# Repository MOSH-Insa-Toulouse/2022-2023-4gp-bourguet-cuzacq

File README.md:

# Projet Capteur de Solène Bourguet et Victor Cuzacq
_Ce projet s’inscrit dans le contexte de l’UF « Du capteur au band de test en open source hardware » du département de Génie Physique de l’INSA Toulouse._  

## Objectif :  
Ce projet se base sur les travaux des chercheurs : Cheng-Wen Lin, Zhibo Zhao, Jaemyung Kim et Jiaxing Huang, afin d’évaluer les potentialités de leur technologie low-tech, le « Pencil Draw Strain Gauges ». L’objectif de ce projet est de réaliser un capteur low-tech à base de graphite et d’en faire une analyse critique argumentée pour en cerner les potentialités et le cas échéant proposer des solutions d’amélioration.  

Pour ce capteur nous utilisons une feuille sur laquelle nous avons dessiner au crayon de papier. La contrainte mécanique appliquée sur la feuille va ainsi modifier la distance entre les particules de graphique et par conséquent la résistance au passage du courant.  

Les étapes et le matériel nécessaire à ce projet sont détaillés ci-dessous.  

## Sommaire  
1. [Livrables](https://github.com/MOSH-Insa-Toulouse/2022-2023-4gp-bourguet-cuzacq#1-livrables)    
2. [Matériel requis](https://github.com/MOSH-Insa-Toulouse/2022-2023-4gp-bourguet-cuzacq#2-mat%C3%A9riel-requis)  
3. [Simulation sur LTSpice](https://github.com/MOSH-Insa-Toulouse/2022-2023-4gp-bourguet-cuzacq#3-simulation-sur-ltspice)  
4. [Kicad](https://github.com/MOSH-Insa-Toulouse/2022-2023-4gp-bourguet-cuzacq#4-kicad)    
  1 [Symboles et empreintes de composants](https://github.com/MOSH-Insa-Toulouse/2022-2023-4gp-bourguet-cuzacq#41-symboles-et-empreintes-de-composants)  
  2 [Schématique](https://github.com/MOSH-Insa-Toulouse/2022-2023-4gp-bourguet-cuzacq#42-sch%C3%A9matique)  
  3 [Placement des composants](https://github.com/MOSH-Insa-Toulouse/2022-2023-4gp-bourguet-cuzacq#43-placement-des-composants)    
  4 [Visualisation 3D](https://github.com/MOSH-Insa-Toulouse/2022-2023-4gp-bourguet-cuzacq#44-visualisation-3d)  
5. [Fabrication du shield](https://github.com/MOSH-Insa-Toulouse/2022-2023-4gp-bourguet-cuzacq#5-fabrication-du-shield)    
  1 [Réalisation du PCB](https://github.com/MOSH-Insa-Toulouse/2022-2023-4gp-bourguet-cuzacq#51-r%C3%A9alisation-du-pcb)    
  2 [Perçage et soudure de nos composants](https://github.com/MOSH-Insa-Toulouse/2022-2023-4gp-bourguet-cuzacq#52-per%C3%A7age-et-soudure-de-nos-composants)    
6. [Arduino](https://github.com/MOSH-Insa-Toulouse/2022-2023-4gp-bourguet-cuzacq#6-arduino)    
  1 [Bibliothèques utilisées](https://github.com/MOSH-Insa-Toulouse/2022-2023-4gp-bourguet-cuzacq#61-biblioth%C3%A8ques-utilis%C3%A9es)    
  2 [Code Arduino](https://github.com/MOSH-Insa-Toulouse/2022-2023-4gp-bourguet-cuzacq#62-code-arduino)    
7. [Application Android](https://github.com/MOSH-Insa-Toulouse/2022-2023-4gp-bourguet-cuzacq#7-application-android)  
8. [Banc de test](https://github.com/MOSH-Insa-Toulouse/2022-2023-4gp-bourguet-cuzacq#8-banc-de-test)    
  1 [Banc de test](https://github.com/MOSH-Insa-Toulouse/2022-2023-4gp-bourguet-cuzacq#81-banc-de-test-1)    
  2 [Résultats obtenus](https://github.com/MOSH-Insa-Toulouse/2022-2023-4gp-bourguet-cuzacq#82-r%C3%A9sultats-obtenus)    
  3 [Analyse des résultats](https://github.com/MOSH-Insa-Toulouse/2022-2023-4gp-bourguet-cuzacq#83-analyse-des-r%C3%A9sultats)    
9. [Pistes d’améliorations](https://github.com/MOSH-Insa-Toulouse/2022-2023-4gp-bourguet-cuzacq#9-pistes-dam%C3%A9liorations)     
10. [Datasheet](https://github.com/MOSH-Insa-Toulouse/2022-2023-4gp-bourguet-cuzacq#10-datasheet)   

## 1. Livrables  
Voici l’ensemble des livrables du projet :  
- Une carte PCB se connectant à un module Arduino UNO contenant un amplification transimpédance, un module Bluetooth, un écran OLED et un Flex sensor  
-	Un code Arduino permettant de mesurer la déformation du capteur et de piloter un module Bluetooth, un écran OLED et un Flex sensor  
-	Une application Android APK  
-	Un protocole de test (simulation sous LTspice + banc de test ?)  
-	La datasheet du capteur de déformation  

Nous avons commencé par réaliser la modélisation de notre shield sur le logiciel Kicad. Il contient ainsi un amplificateur transimpédance, un écran OLED, un module Bluetooth et un Flex sensor. Nous avons ensuite fabriqué par lithographie notre carte PCB et ajouté les composants par soudage sur la carte après l’avoir percée au préalable. 
Nous avons réalisé un code Arduino permettant de mesurer la variation de résistance du capteur et de piloter un module Bluetooth, un écran OLED et un Flex sensor.  

En parallèle de cela, nous avons créé une application Android grâce au logiciel MIT App Inventor, capable de communiquer avec le module Bluetooth et recevoir la valeur de la tension de sortie et de calculer les valeurs de résistances de notre capteur.  

Par la suite nous avons mis en place un banc de test pour caractériser notre capteur en fonction de sa déformation et de la mine de crayon utilisée (HB, B).   

Pour finir nous avons réalisé une datasheet à l’aide des résultats obtenus par le banc de test.   

## 2. Matériel requis

Voici la liste des composants nécessaires à l’élaboration de notre capteur   

-	2 résistances 100kΩ (R1 et R3)    
-	1 résistance 10kΩ (R5) (R4 sur notre Kicad)  
-	2 résistances 1kΩ (R2 et R6) (R2 et R5 sur notre Kicad)  
-	1 résistance de 33kΩ (Rflex)  
-	1 capacité 1µF (C4)  
-	2 capacités 100nF (C1 et C2)   
-	1 amplificateur opérationnel LTC1050  
-	1 module Bluetooth HC05   
-	1 écran OLE I2C 0.91  
-	1 Flex sensor   
-	1 feuille de papier  
-	3 crayon de papier : HB, B  

## 3. Simulation sur LTspice 

Le capteur graphique que nous souhaitons réalisé est alimenté en 5V et sa résistance fluctue entre 20 et 100MΩ, ainsi le courant en sortie sera de l’ordre de 100nA (I =U/R). Ce courant de sortie sera trop faible pour être capté par la carte Arduino UNO, c’est pourquoi nous devons utiliser un amplificateur transimpédance, pour amplifier le signal de sortie de notre capteur. 

Ce montage gère à la fois l’amplification et le filtrage du signal pour limiter l’amplification du bruit.

Voici la fonction des différents composants :
  - R5 en entrée protège l'ampli opérationnel contre les décharges électrostatiques, en forme avec C1 un filtre pour les bruits en tension  
  - C1 avec R1 forme un filtre pour le bruit en courant  
  - R2 sera interchangeable, pour permettre une adaptation du calibre  
  - C4 avec R3 forme un filtre actif  
  - C2 avec R6 forme le filtre de sortie 
  
On peut calculer la résistance du capteur grâce à la formule :

$R_{Capteur} = (1 + \dfrac{R3}{R2}) \times R1 \times (\dfrac{VCC}{VADC}) - R1 - R5$  

Dans notre code Arduino ainsi que dans notre Kicad, notre R4 est égale au R5 du schéma ci-contre et R5 vaut R6 du schéma.   

## 4. Kicad

Nous avons modélisé notre shield PCB sur le logiciel KICAD. Nous avons commencé par dessiner tous les composants puis nous avons créé leur empreinte.  

### 4.1 Symboles et empreintes de composants   

- Amplificateur LTC1050  

- Ecran OLED  

- Flex sensor  

- Module Bluetooth HC05  

### 4.2 Schématique  

Une fois les empreintes créées, nous avons réalisé le schéma de notre shield.  

### 4.3 Placement des composants  

### 4.4 Visualisation 3D  

Nous avons téléchargé les modèles 3D de nos composants afin de visualiser notre PCB en 3D et de vérifier que les composants de la carte ne se chevauchent pas.   

## 5. Fabrication du shield  

### 5.1 Réalisation du PCB  

Nous avons réalisé notre PCB avec l’aide de Catherine Crouzet au sein du département du Génie Physique et du Génie Electrique et Informatique de l’INSA Toulouse. Pour fabriquer notre PCB nous avons utilisé une plaquette d’époxy recouverte d’une fine couche de cuivre. Nous avons d’abord imprimé notre modélisation du PCB réalisé sur Kicad. Nous avons ensuite plongé notre plaquette avec notre modélisation imprimée dans une machine insolant des UVs.  
Notre modélisation imprimée va servir de masque lors de cette insolation sous UVs. A l’aide d’un révélateur, nous avons retiré la partie de la résine non insolée. Nous plongeons ensuite la plaquette dans un bain de perchlorure de fer pour la gravure. Le cuivre non protégé par la résine est éliminé. Pour finir, nous lavons notre plaquette à l’acétone pour éliminer les dernières traces de résine.   

### 5.2 Perçage et soudure de nos composants   

Nous perçons ensuite notre PCB à l’aide d’une perceuse électrique pour insérer nos composants. Le diamètre de nos percage varie selon le type de composant :   
-	0,8 mm : pour l’AOP LTC1050, le module OLED, Bluetooth, le Flex sensor, les résistances et les capacités
-	1,0 mm : pour les broches de connexion de la carte Arduino UNO.  
Nous avons soudé nos composants sur la face arrière du PCB. Nous avons cependant constaté des courts-circuits sur la carte PCB qui nous ont obligé à souder des fils reliés à la masse sur la face avant de notre PCB.  

## 6. Arduino  

### 6.1 Bibliothèques utilisées    

Nous avons utilisé 3 bibliothèques dans notre code Arduino :  
-	Wire.h : qui s’occupe de la communication avec l’écran OLED ;  
-	SoftwareSerial.h : pour définir les ports utilisés par le module Bluetooth ;  
-	Adafruit_SSD1306.h : afin de contrôler notre écran OLED.   

### 6.2 Code Arduino   

Notre code permet de récupérer la tension à la sortie du capteur et de calculer la valeur de sa résistance. Nous avons rajouté des éléments sur le shield pour faciliter la communication de l’information :    
-	Un écran OLED : l’écran reçoit la valeur de la résistance (en MΩ) du capteur en continu 
-	Un module Bluetooth : qui envoie les données à l’application  
-	Un Flex sensor : dont la valeur de la résistance et la valeur de son angle sont affichés dans le Serial Monitor. Sa présence nous permet de vérifier les démarches réalisées sur le capteur.  

## 7. Application Android   

Nous avons créé une application android sur Mit App Inventor que nous avons pu télécharger via le .apk du dossier. 
Le but de notre application est d’afficher la valeur de la tension de sortie du capteur en continu sur un téléphone Android et de tracer un graphique de la valeur de sa résistance en fonction du temps. C’est l’application qui va calculer la valeur de la résistance du capteur. 
Notre interface comprend :  
-	Un bouton connexion au Bluetooth de notre shield. Il devient vert quand la connexion est établie et grise quand elle ne l’est pas.   
-	Un bouton déconnexion au Bluetooth. Il devient rouge quand on appuie dessus.  
-	La valeur de la tension de sortie du capteur en continu.   
-	Un graphique affichant la valeur de la résistance de notre capteur en fonction du temps.   

## 8. Banc de test   

### 8.1 Banc de test   

Nous avons testé notre capteur sur un banc de test disponible au Génie Physique de l’INSA Toulouse. Notre banc de test composé de 7 demi cylindres de rayon allant de 2,5cm à 1cm par pas de 0,5cm.   

En enrobant les cylindres avec notre capteur, nous créons une déformation que nous pouvons calculer avec la formule :   

$\epsilon = \dfrac{e}{2 \times R_{Capteur}}$   

avec l’épaisseur du papier : e = 0,3 mm et l’angle de la deformation : θ  

et $R_{Capteur} = \dfrac{d}{2 \times θ}$  

La contrainte mécanique (compression ou expansion) appliquée au papier va modifier la distance entre les particules de graphite et donc la résistance au passage du courant :  
-	Lorsque l’on enrobe le cylindre avec la face recouverte de graphite vers le haut, nous appliquons une tension ou expansion à notre papier, ainsi les particules de graphite se retrouve plus éloignées. Par conséquent le courant circule moins facilement et la valeur de la résistance augmente.   
-	A l’inverse, lorsque l’on enrobe le cylindre avec la face recouverte de graphite contre le cylindre, nous appliquons une compression à notre papier, ainsi les particules de graphite se rapprochent. Par conséquent le courant circule plus facilement et la valeur de la résistance diminue.   

_Attention : Plus nous utilisons la jauge de contrainte, plus nous l’abîmons. En effet, la quantité de graphite diminue avec le temps à cause du frottement des pinces en métal ou des doigts avec le papier._   

### 8.2 Résultats obtenus  

La caractérisation de notre capteur est basé sur la mesure des variations de la résistance dû à la déformation.  

### 8.3 Analyse des résultats   

Les résultats obtenus semblent cohérents. En effet, on observe bien une résistance qui diminue lorsqu’on applique une compression au capteur. Par conséquent ΔR (=R-R0) diminue plus la déformation est grande. Et à l’inverse on observe une résistance grandissante lorsqu’on applique une expansion à notre capteur. Par conséquent ΔR (=R-R0) augmente plus la déformation est importante.  

De plus, en fonction du type de crayon utilisé, les variations de résistances changent. En effet, si un crayon est considéré comme gras c’est qu’il dépose plus de graphite sur le papier. Par conséquent le courant aura plus de facilité à passer et donc la résistance sera plus faible. Ainsi nous pouvons constater que les crayons de type B sont plus gras que les crayons de type HB.   

### 8.4 Comparaison avec le flex sensor  

Nous avons analysé la variation de la résistance du flex sensor pour le comparer avec notre capteur. Nous pouvons constater que le flex sensor possède une valeur de résistance plus importante que notre capteur de graphite.   

## 9. Pistes d'améliorations 

Certains points de notre banc de test peuvent être remis en question :  
-	Le dépôts de graphite est difficile à maîtriser. Par conséquent il est impossible de créer plusieurs jauge de contraintes identiques. De plus, la quantité de graphite diminue avec le temps à cause du frottement des pinces en métal ou des doigts avec le papier.  
-	Nous aurions pu rajouter sur notre shield un potentiomètre digital qui nous aurait permis de pouvoir analyser une gamme de résistance plus grande.   

## 10. Datasheet  

La datasheet de notre capteur est disponible [ICI](https://github.com/MOSH-Insa-Toulouse/2022-2023-4gp-bourguet-cuzacq/blob/main/Datasheet/Datasheet_low_tech_graphitr_based_on_strain_sensor.pdf).  

### Remerciement et contact 

Nous souhaiterions remercier Catherine Crouzet qui nous a beaucoup aidé à comprendre et à solutionner nos problèmes tout au long du projet.  

Pour toutes questions ou informations supplémentaires, vous pouvez nous contacter par mail :  
-	Solène BOURGUET : bourguet@insa-toulouse.fr   
-	Victor CUZACQ : cuzacq@insa-toulouse.fr

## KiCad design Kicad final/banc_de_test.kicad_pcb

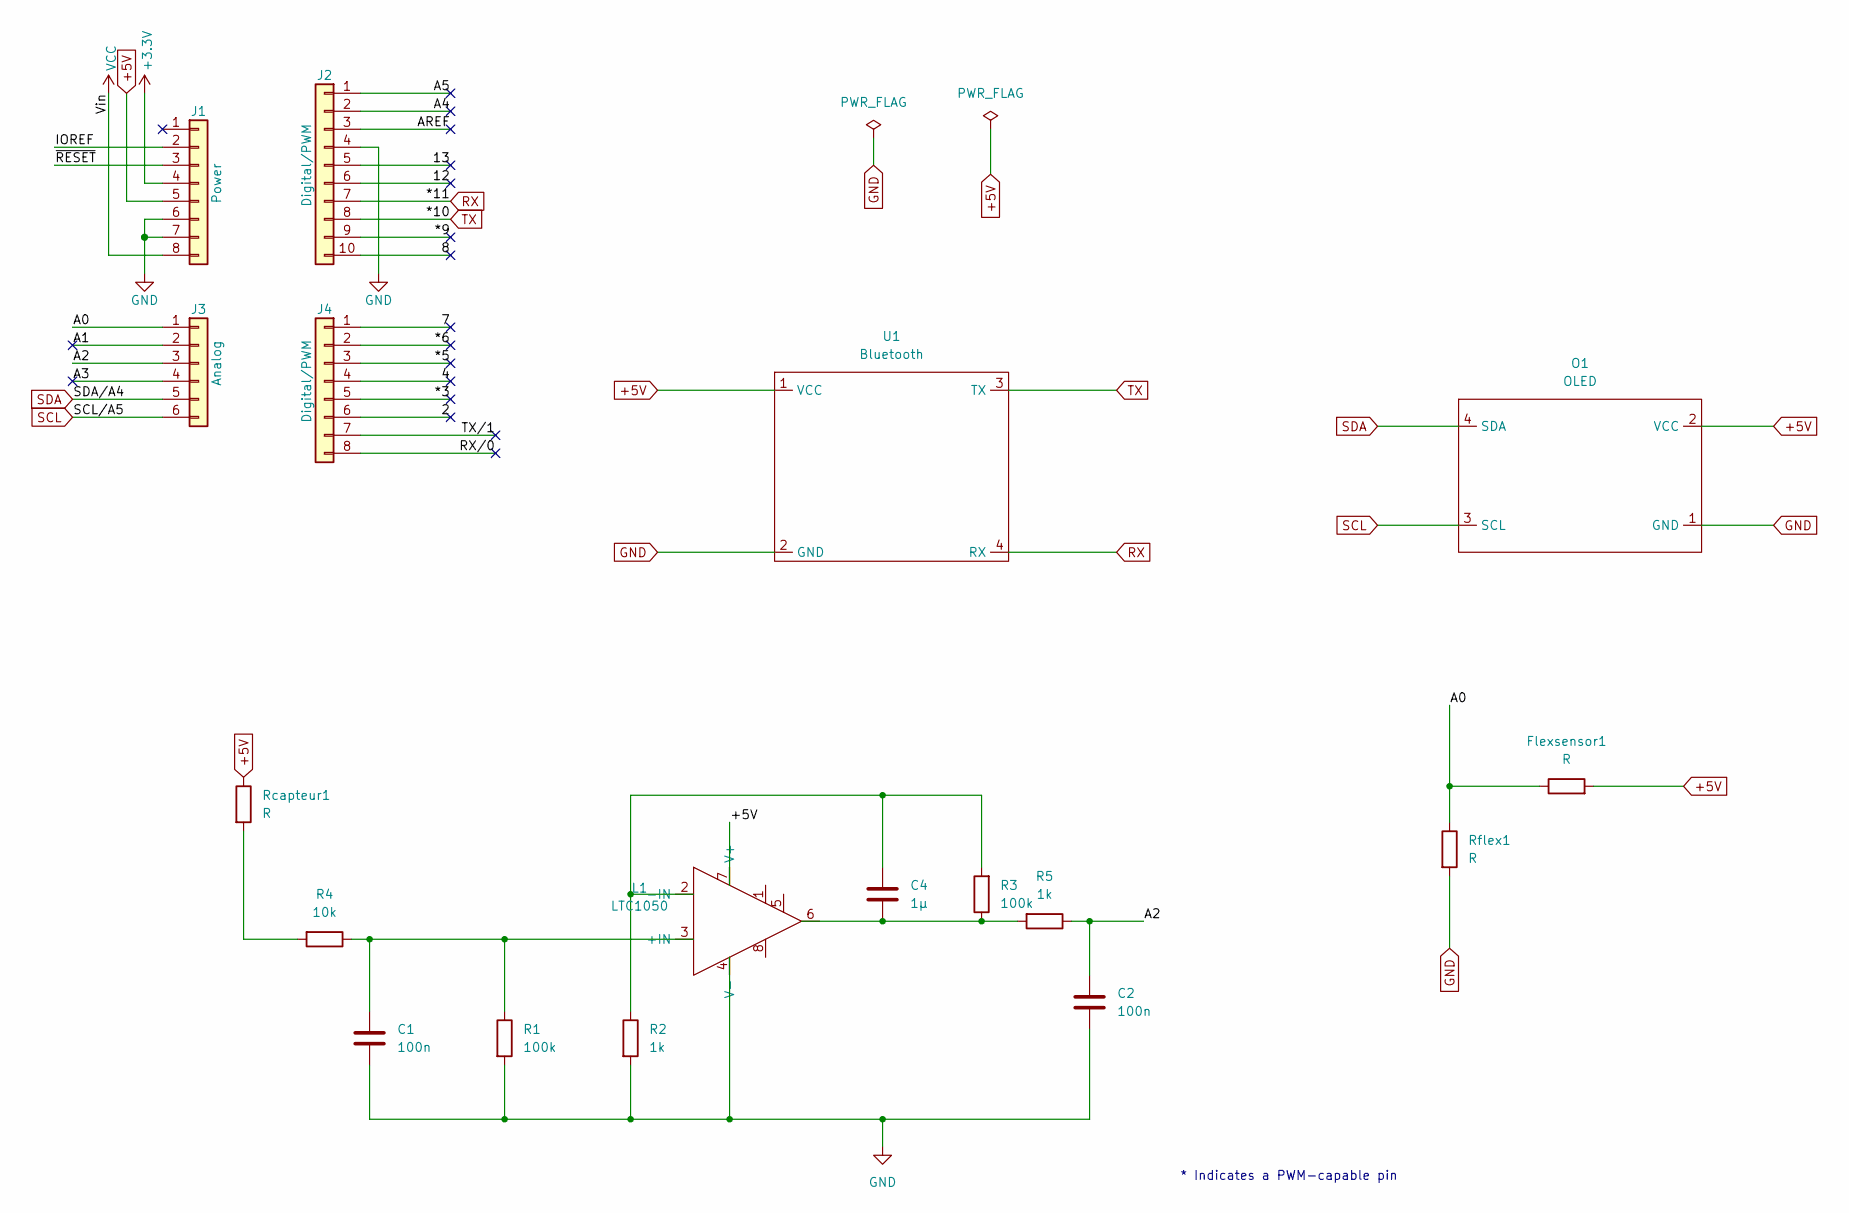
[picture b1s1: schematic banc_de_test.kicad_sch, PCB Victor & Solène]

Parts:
C1, C2: 100n; C_Disc_D3.0mm_W1.6mm_P2.50mm
C4: 1µ; C_Rect_L7.0mm_W4.5mm_P5.00mm
Flexsensor1: R; R_Axial_DIN0204_L3.6mm_D1.6mm_P2.54mm_Vertical
J1: Power; PinSocket_1x08_P2.54mm_Vertical
J2: Digital/PWM; PinSocket_1x10_P2.54mm_Vertical
J3: Analog; PinSocket_1x06_P2.54mm_Vertical
J4: Digital/PWM; PinSocket_1x08_P2.54mm_Vertical
L1: LTC1050
O1: OLED
R1, R3: 100k; R_Axial_DIN0204_L3.6mm_D1.6mm_P2.54mm_Vertical
R2, R5: 1k; R_Axial_DIN0204_L3.6mm_D1.6mm_P2.54mm_Vertical
R4: 10k; R_Axial_DIN0204_L3.6mm_D1.6mm_P2.54mm_Vertical
Rcapteur1: R; R_Axial_DIN0204_L3.6mm_D1.6mm_P2.54mm_Vertical
Rflex1: R; R_Axial_DIN0204_L3.6mm_D1.6mm_P2.54mm_Vertical
U1: Bluetooth

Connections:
+3V3: J1.4
+5V: Flexsensor1.2, J1.5, L1.7 (V+), O1.2 (VCC), Rcapteur1.1, U1.1 (VCC)
/2: J4.6
/4: J4.4
/7: J4.1
/8: J2.10
/12: J2.6
/13: J2.5
/*3: J4.5
/*5: J4.3
/*6: J4.2
/*9: J2.9
/A0: Flexsensor1.1, J3.1, Rflex1.1
/A1: J3.2
/A2: C2.1, J3.3, R5.1
/A3: J3.4
/A4: J2.2
/A5: J2.1
/AREF: J2.3
/IOREF: J1.2
/RX/0: J4.8
/TX/1: J4.7
/~RESET: J1.3
GND: C1.2, C2.2, J1.6, J1.7, J2.4, L1.4 (V-), O1.1 (GND), R1.2, R2.2, Rflex1.2, U1.2 (GND)
unnamed: C1.1, L1.3 (+IN), R1.1, R4.1
unnamed: C4.1, L1.2 (-IN), R2.1, R3.2
unnamed: C4.2, L1.6, R3.1, R5.2
unnamed: R4.2, Rcapteur1.2
RX: J2.7, U1.4 (RX)
SCL: J3.6, O1.3 (SCL)
SDA: J3.5, O1.4 (SDA)
TX: J2.8, U1.3 (TX)
VCC: J1.8

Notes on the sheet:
* Indicates a PWM-capable pin

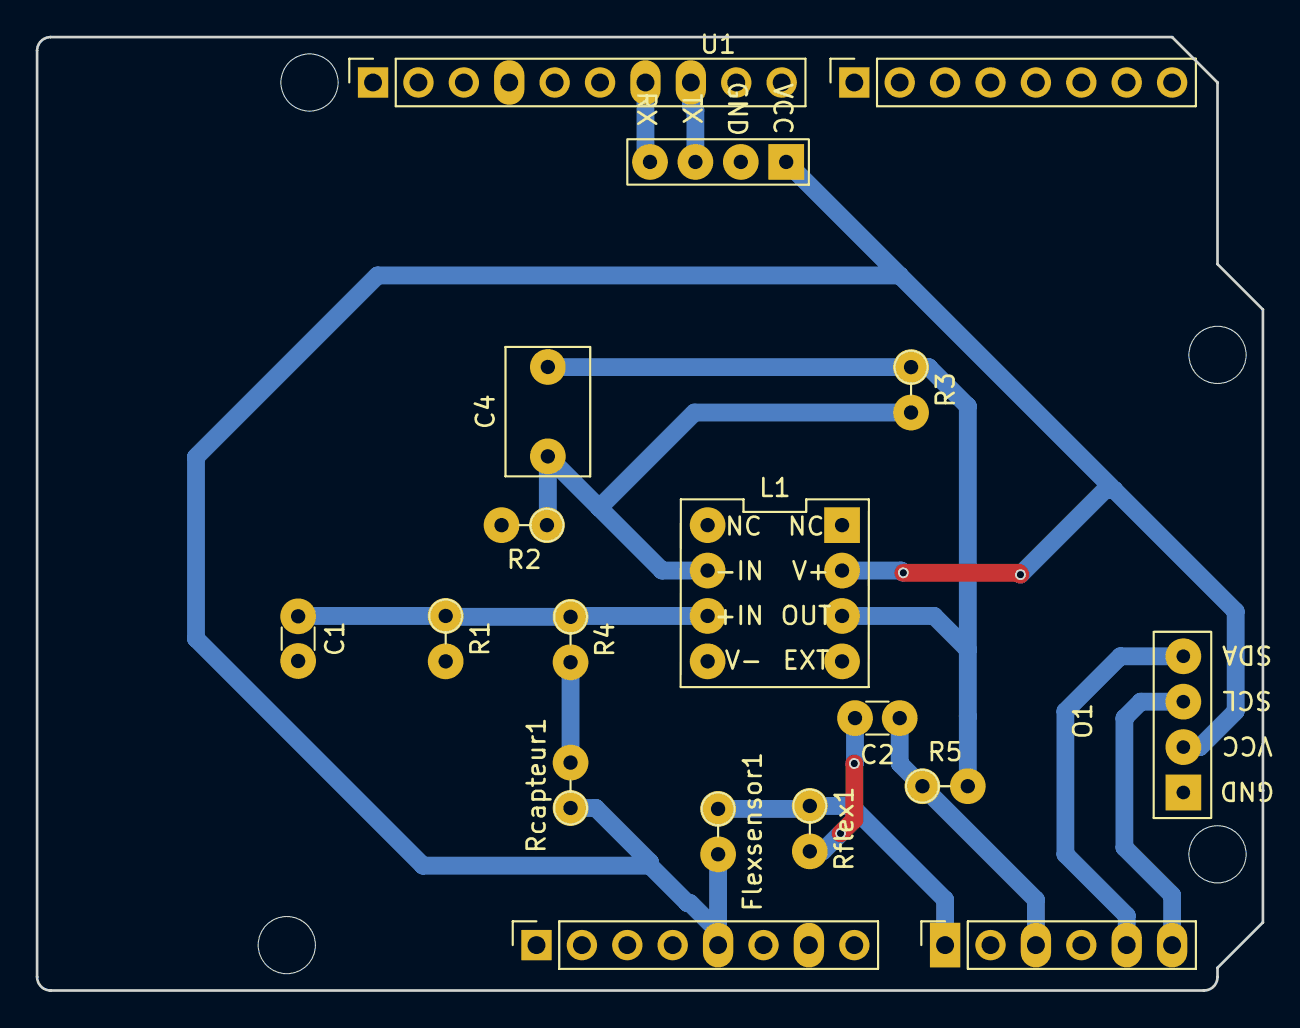
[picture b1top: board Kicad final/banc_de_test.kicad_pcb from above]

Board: 2 copper layers, 68.6 x 53.3 mm, 22 parts (0 on the bottom side), 12 nets.

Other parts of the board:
MH1, MH2, MH3, MH4: MountingHole_3.2mm

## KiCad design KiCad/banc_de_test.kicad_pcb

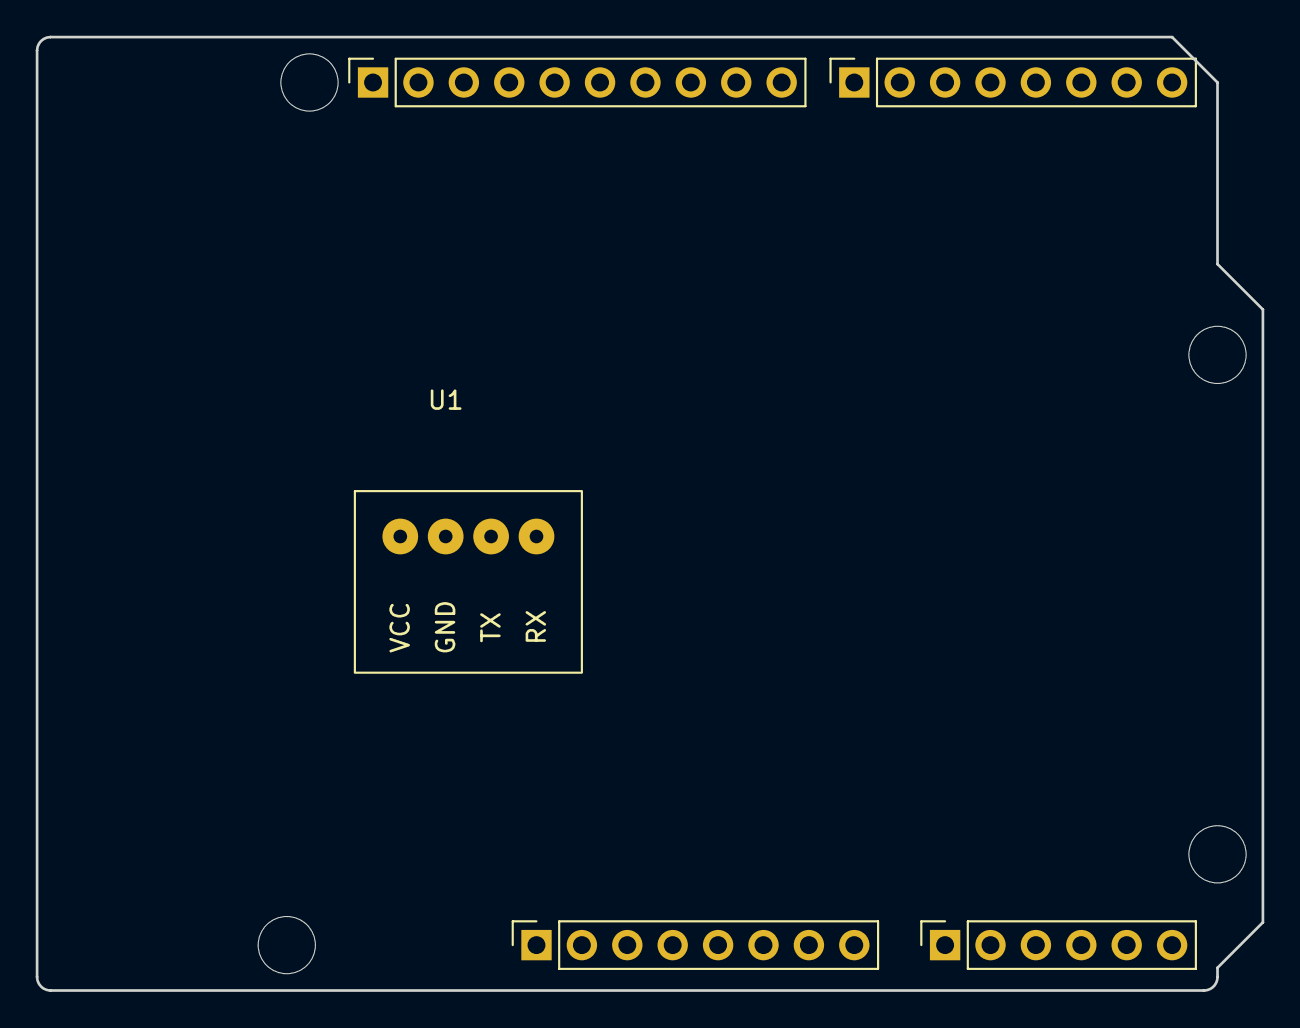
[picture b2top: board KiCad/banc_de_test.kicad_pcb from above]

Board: 2 copper layers, 68.6 x 53.3 mm, 9 parts (0 on the bottom side), 4 nets, no tracks yet.

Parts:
J1: Power; PinSocket_1x08_P2.54mm_Vertical
J2: Digital/PWM; PinSocket_1x10_P2.54mm_Vertical
J3: Analog; PinSocket_1x06_P2.54mm_Vertical
J4: Digital/PWM; PinSocket_1x08_P2.54mm_Vertical
MH1, MH2, MH3, MH4: MountingHole_3.2mm
U1: Bluetooth

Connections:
/SCL/A5: J2.1, J3.6
/SDA/A4: J2.2, J3.5
GND: J1.6, J1.7, J2.4
VCC: J1.8, U1.1 (VCC)

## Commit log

2023-03-04 ajout Kicad
2023-03-04 màj readme.md
2023-03-18 kicad final ajout
2023-05-15 final commit
2023-05-23 images
